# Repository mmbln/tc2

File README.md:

# tc2
garden lamp controller

This is a project which is about a pcb and its software that controls two lamps in my garden. The lamps are switched on when the sun goes down and switched off when the sun comes up.

The times of the sunset and sunrise are fetched from the internet. Also the current time is fetched from the internet. The main controller is an ARM microprocesser (LPC1114). The network connection is done by a wifi interface (ESP8266).

The pcb is designed with kicad. The microcontroller program will be written in C (not checked in yet). Be patient.

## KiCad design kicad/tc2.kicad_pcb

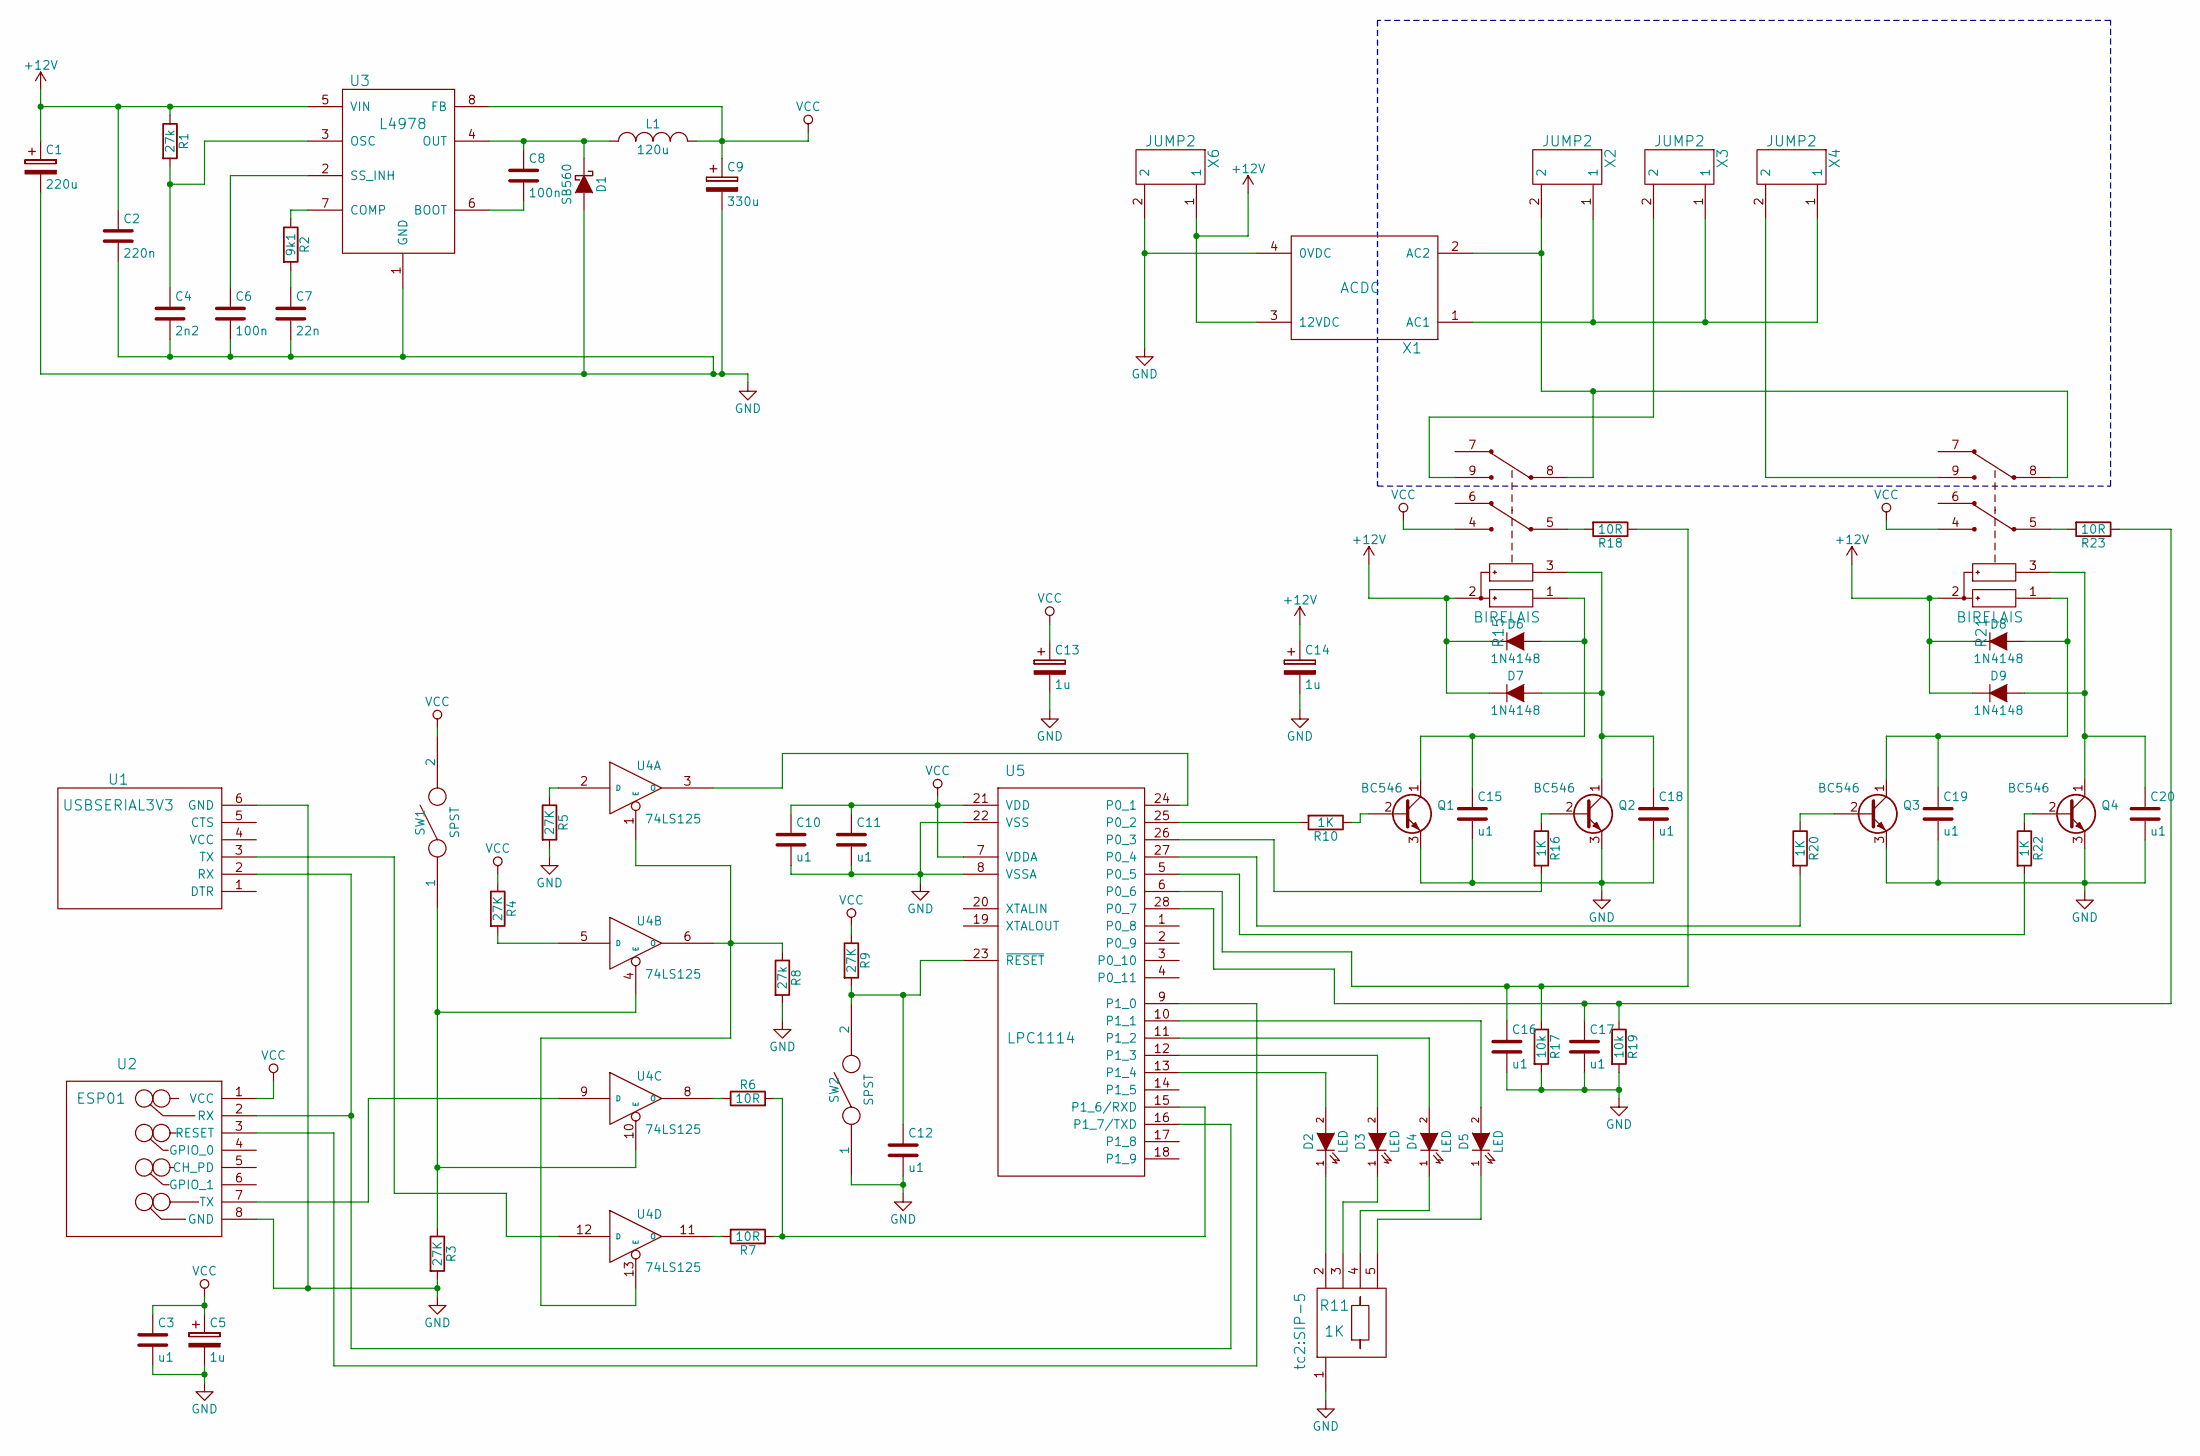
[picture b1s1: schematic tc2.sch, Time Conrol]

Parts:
C1: 220u; C_Radial_D10_L13_P5
C2: 220n; C_Rect_L7_W2_P5
C3, C10, C11, C12, C15, C16, C17, C18, C19, C20: u1; C_Rect_L7_W2_P5
C4: 2n2; C_Rect_L7_W2_P5
C5, C13, C14: 1u; C_Radial_D5_L11_P2
C6, C8: 100n; C_Rect_L7_W2_P5
C7: 22n; C_Rect_L7_W2_P5
C9: 330u; C_Radial_D10_L13_P5
D1: SB560; Diode_DO-41_SOD81_Horizontal_RM10
D2, D3, D4, D5: LED; LED-3MM
D6, D7, D8, D9: 1N4148; Diode_DO-35_SOD27_Horizontal_RM10
L1: 120u; L100
Q1, Q2, Q3, Q4: BC546; TO-92_Molded_Narrow
R1, R8: 27k; R4
R2: 9k1; R4
R3, R4, R5, R9: 27K; R4
R6, R7, R18, R23: 10R; R4
R10, R16, R20, R22: 1K; R4
R11: 1K; SIP-5
R15, R21: BIRELAIS; bistabilrelais
R17, R19: 10k; R4
SW1: SPST; Switch
SW2: SPST; taster
U1: USBSERIAL3V3; SIPSerial
U2: ESP01; esp01
U3: L4978; DIP-8_W7.62mm
U4: 74LS125; SOIC-14_3.9x8.7mm_Pitch1.27mm
U5: LPC1114; DIP-28_W15.24mm
X1: ACDC
X2, X3, X4, X6: JUMP2; schraubklemme2

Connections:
+12V: C1.1, C2.1, C14.1, D6.1 (K), D7.1 (K), D8.1 (K), D9.1 (K), R1.1, R15.2, R21.2, U3.5 (VIN), X1.3 (12VDC), X6.1
GND: C1.2, C2.2, C3.2, C4.2, C5.2, C6.2, C7.2, C9.2, C10.2, C11.2, C12.2, C13.2, C14.2, C15.2, C16.2, C17.2, C18.2, C19.2, C20.2, D1.2 (A), Q1.3 (E), Q2.3 (E), Q3.3 (E), Q4.3 (E), R3.2, R5.2, R8.2, R11.1, R17.2, R19.2, SW2.1, U1.6 (GND), U2.8 (GND), U3.1 (GND), U4.7 (GND), U5.8 (VSSA), U5.22 (VSS), X1.4 (0VDC), X6.2
unnamed: C4.1, R1.2, U3.3 (OSC)
unnamed: C6.1, U3.2 (SS_INH)
unnamed: C7.1, R2.2
unnamed: C8.1, D1.1 (K), L1.1, U3.4 (OUT)
unnamed: C8.2, U3.6 (BOOT)
unnamed: C12.1, R9.2, SW2.2, U5.23 (~RESET)
unnamed: C15.1, D6.2 (A), Q1.1 (C), R15.1
unnamed: C16.1, R17.1, R18.1, U5.6 (P0_6)
unnamed: C17.1, R19.1, R23.1, U5.28 (P0_7)
unnamed: C18.1, D7.2 (A), Q2.1 (C), R15.3
unnamed: C19.1, D8.2 (A), Q3.1 (C), R21.1
unnamed: C20.1, D9.2 (A), Q4.1 (C), R21.3
unnamed: D2.1 (K), R11.2
unnamed: D2.2 (A), U5.13 (P1_4)
unnamed: D3.1 (K), R11.3
unnamed: D3.2 (A), U5.12 (P1_3)
unnamed: D4.1 (K), R11.4
unnamed: D4.2 (A), U5.11 (P1_2)
unnamed: D5.1 (K), R11.5
unnamed: D5.2 (A), U5.10 (P1_1)
unnamed: Q1.2 (B), R10.1
unnamed: Q2.2 (B), R16.1
unnamed: Q3.2 (B), R20.1
unnamed: Q4.2 (B), R22.1
unnamed: R2.1, U3.7 (COMP)
unnamed: R3.1, SW1.1, U4.4 (E), U4.10 (E)
unnamed: R4.2, U4.5 (D)
unnamed: R5.1, U4.2 (D)
unnamed: R6.1, U4.8 (O)
unnamed: R6.2, R7.1, U5.15 (P1_6/RXD)
unnamed: R7.2, U4.11 (O)
unnamed: R8.1, U4.1 (E), U4.6 (O), U4.13 (E)
unnamed: R10.2, U5.25 (P0_2)
unnamed: R15.5, R18.2
unnamed: R15.8, R21.8, X1.2 (AC2), X2.2
unnamed: R15.9, X3.2
unnamed: R16.2, U5.26 (P0_3)
unnamed: R20.2, U5.27 (P0_4)
unnamed: R21.5, R23.2
unnamed: R21.9, X4.2
unnamed: R22.2, U5.5 (P0_5)
unnamed: U1.2 (RX), U2.2 (RX), U5.16 (P1_7/TXD)
unnamed: U1.3 (TX), U4.12 (D)
unnamed: U2.3 (RESET), U5.9 (P1_0)
unnamed: U2.7 (TX), U4.9 (D)
unnamed: U4.3 (O), U5.24 (P0_1)
unnamed: X1.1 (AC1), X2.1, X3.1, X4.1
VCC: C3.1, C5.1, C9.1, C10.1, C11.1, C13.1, L1.2, R4.1, R9.1, R15.4, R21.4, SW1.2, U2.1 (VCC), U3.8 (FB), U4.14 (VCC), U5.7 (VDDA), U5.21 (VDD)

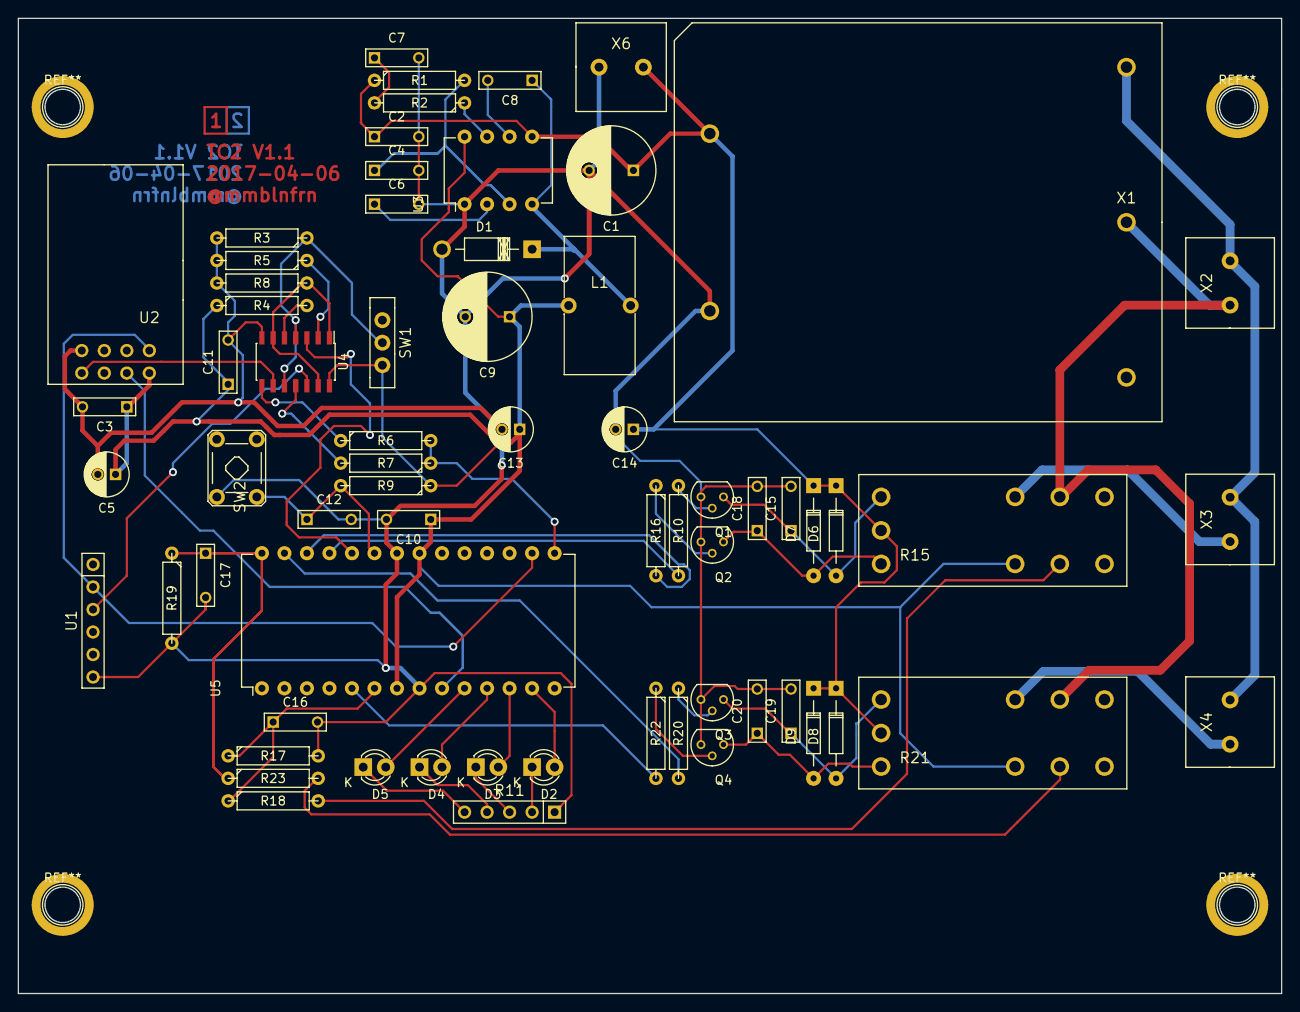
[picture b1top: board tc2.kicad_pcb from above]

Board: 2 copper layers, 142.5 x 110.0 mm, 66 parts (0 on the bottom side), 50 nets.

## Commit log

2017-04-05 initial commit
    V1.0 Release Candidate
2017-04-05 minor correction for gerber files
    Added some reference marks
2017-04-05 Version 1.0 Generated gerberfiles for production
    made minor changes in the dimension drawing.
2017-04-06 Added some dimension drawing.
    Version tagged as 1.1
2017-04-07 Added README.md
    First commit to github.
2017-04-07 start the software
    very simple main.c created.
